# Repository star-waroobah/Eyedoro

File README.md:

## EyeDoro!

Eyedoro is a desk buddy with two robot eyes that works as a Pomodoro study timer. Press the button to start a 25 minute work session. While you work, the eyes look around as if they are watching over you. When time is up, a beep plays and the eyes fall asleep for a 5 minute break, then a lower beep wakes them up.

I made Eyedoro because I wanted a study timer that felt more like a little desk companion instead of just another boring countdown. Sometimes it's hard to stay focused while studying, so I thought having a pair of animated robot eyes watching over my desk would make studying a little more fun.
For Hack Club Half Life Week 4, I wanted to experiment with LED displays. I also wanted to learn more about programming microcontrollers, working 
with buttons and buzzers, and making different components work together.

### How It Works
- **Study Mode (25 Minutes):** Press the button to start a study session. The robot's eyes randomly look left, right, up, and down while occasionally blinking.
- **Break Mode (5 Minutes):** When the study session ends, the buzzer plays a high-pitched alert and the eyes close to sleep.
- **Wake-Up Alert:** After the break ends, a lower-pitched beep plays and the robot wakes up, ready for another study session.
- **Pause/Resume:** Press the button during a session to pause the timer, and press it again to resume.

A Seeed XIAO RP2040 drives two 8x8 MAX7219 LED matrix modules (the eyes) over SPI. A 74AHCT125 level shifter turns the XIAO's 3.3 V signals into the 5 V signals the MAX7219 needs. A button starts and pauses the timer and a passive buzzer plays the alerts.

### Technical Details
- **Microcontroller:** Seeed Studio XIAO RP2040
- **Displays:** 2 × MAX7219 8×8 LED Matrix Modules
- **Communication:** SPI
- **Level Shifter:** 74AHCT125 (3.3V to 5V)
- **Input:** Push Button
- **Audio:** Passive Buzzer
- **Programming Language:** Arduino C++
- **Timer:** `millis()`-based countdown
- **Sound Generation:** `tone()` function

## PCB

## Schematic

## 3D view

## Bill of materials
- 1x Seeed XIAO RP2040
- 2x single 8x8 MAX7219 module
- 1x 74AHCT125 (SOIC-14)
- 1x 10 uF capacitor (0805)
- 1x 100 nF capacitor (0805)
- 1x push button (6 mm)
- 1x passive buzzer
- 1x 5-pin male header (J1)

## Firmware

The firmware for **Eyedoro** is written in **Arduino C++** and designed to run on the **Seeed Studio XIAO RP2040**.
It uses the **MD_MAX72XX** library and RobotEyes animations to control two MAX7219 8×8 LED matrix displays.

### Firmware Files
| File | Description |
|------|-------------|
| `Eyedoro.ino` | Main Arduino sketch containing the Pomodoro timer, button controls, and buzzer alerts. |
| `MD_RobotEyes.cpp` | Handles the robot eye animations. |
| `MD_RobotEyes.h` | Contains the eye animation class definitions. |
| `MD_RobotEyes_Data.h` | Stores the eye graphics and animation sequences. |

The firmware has been written and reviewed, but it has not yet been tested on the physical hardware. Final compilation, uploading, and hardware testing are still pending.

## Credits
A big thanks to the following projects and communities that helped in making Eyedoro!

- **[Hack Club Half Life](https://halflife.hackclub.com/)** – For organizing the hardware challenge and inspiring me to build something creative using LED displays.
- **[MajicDesigns – MD_MAX72XX](https://github.com/MajicDesigns/MD_MAX72XX)** – For the LED matrix library and original RobotEyes animation example that I used as a starting point.

## Status
Designed in week 4 of Half Life. The build is planned for week 9.

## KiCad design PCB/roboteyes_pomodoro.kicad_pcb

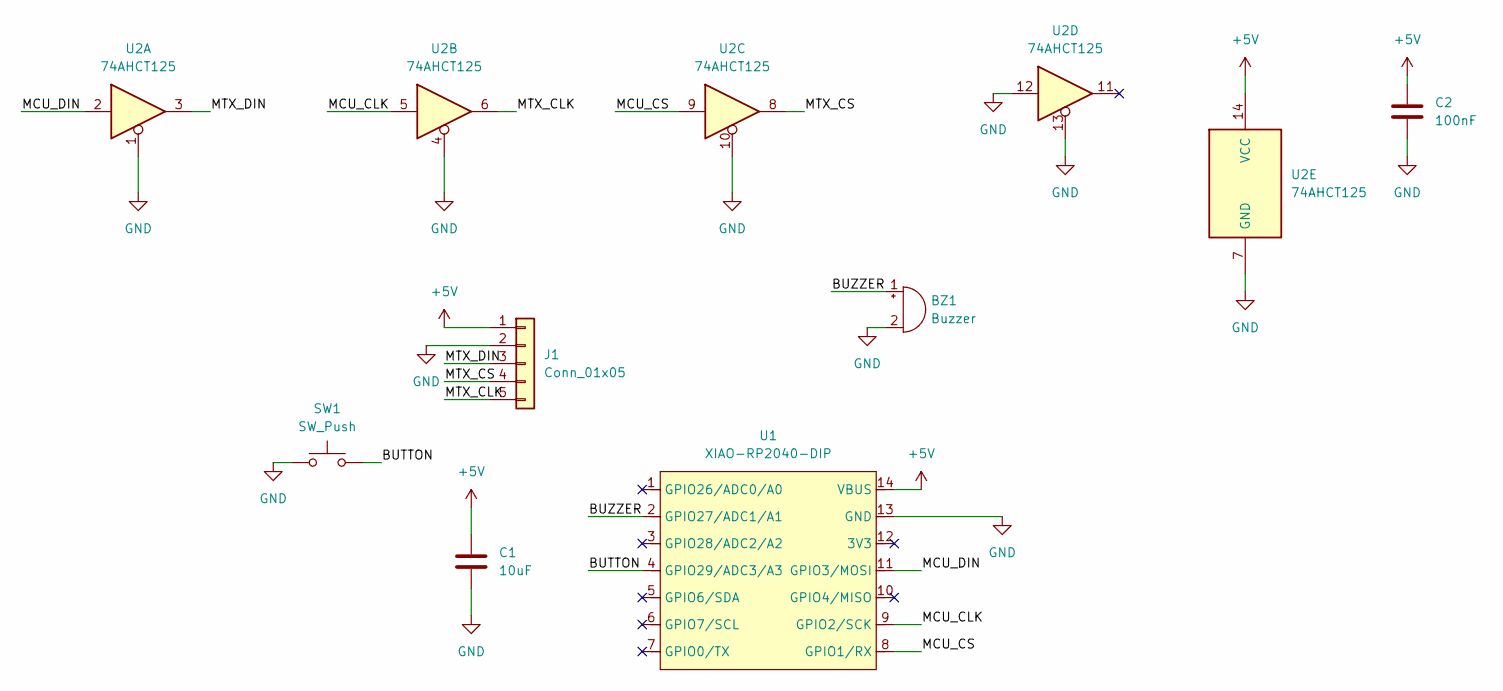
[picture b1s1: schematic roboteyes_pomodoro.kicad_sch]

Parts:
BZ1: Buzzer; Buzzer_12x9.5RM7.6
C1: 10uF; C_0805_2012Metric
C2: 100nF; C_0805_2012Metric
J1: Conn_01x05; PinSocket_1x05_P2.54mm_Vertical
SW1: SW_Push; SW_PUSH_6mm
U1: XIAO-RP2040-DIP
U2: 74AHCT125; SOIC-14_3.9x8.7mm_P1.27mm

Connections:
+5V: C1.1, C2.1, J1.1, U1.14 (VBUS), U2.14 (VCC)
/BUTTON: SW1.2, U1.4 (GPIO29/ADC3/A3)
/BUZZER: BZ1.1 (+), U1.2 (GPIO27/ADC1/A1)
/MCU_CLK: U1.9 (GPIO2/SCK), U2.5
/MCU_CS: U1.8 (GPIO1/RX), U2.9
/MCU_DIN: U1.11 (GPIO3/MOSI), U2.2
/MTX_CLK: J1.5, U2.6
/MTX_CS: J1.4, U2.8
/MTX_DIN: J1.3, U2.3
GND: BZ1.2 (-), C1.2, C2.2, J1.2, SW1.1, U1.13 (GND), U2.1, U2.4, U2.7 (GND), U2.10, U2.12, U2.13

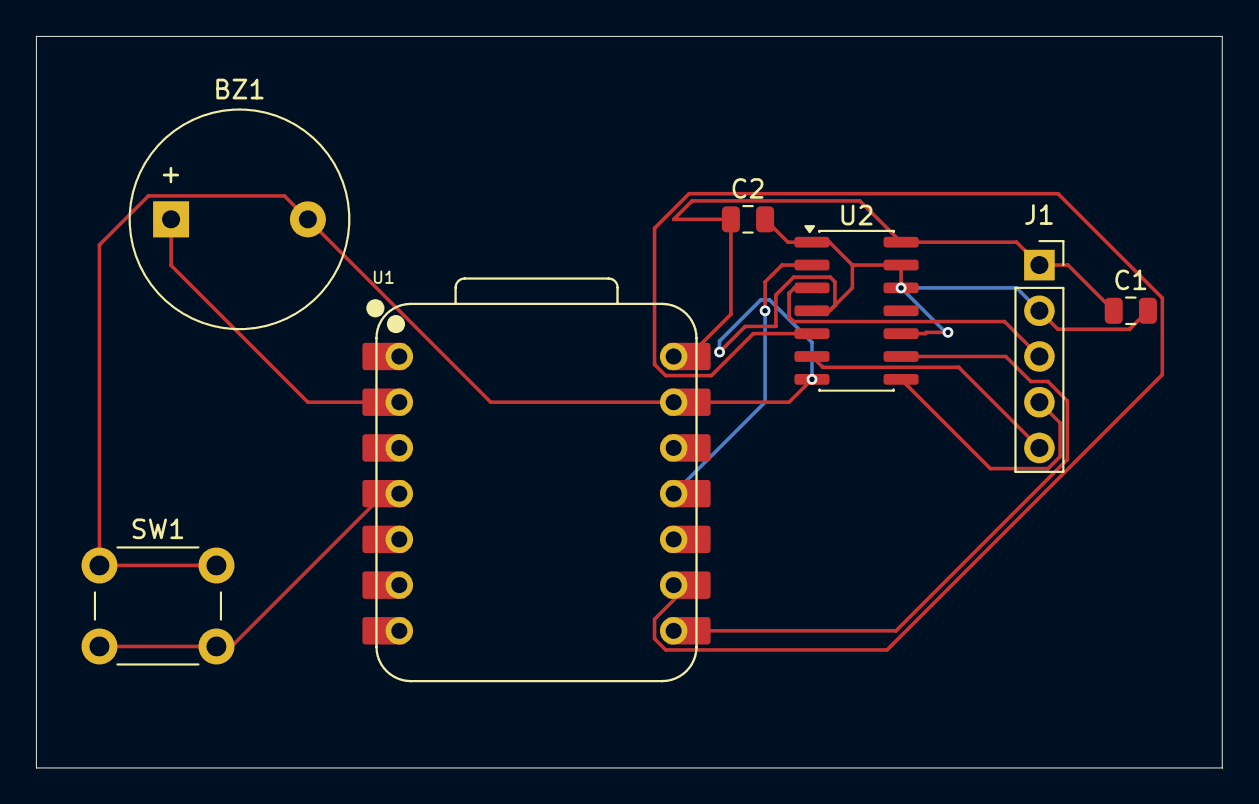
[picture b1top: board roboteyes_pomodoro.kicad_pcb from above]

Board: 2 copper layers, 65.9 x 40.6 mm, 7 parts (0 on the bottom side), 10 nets.
